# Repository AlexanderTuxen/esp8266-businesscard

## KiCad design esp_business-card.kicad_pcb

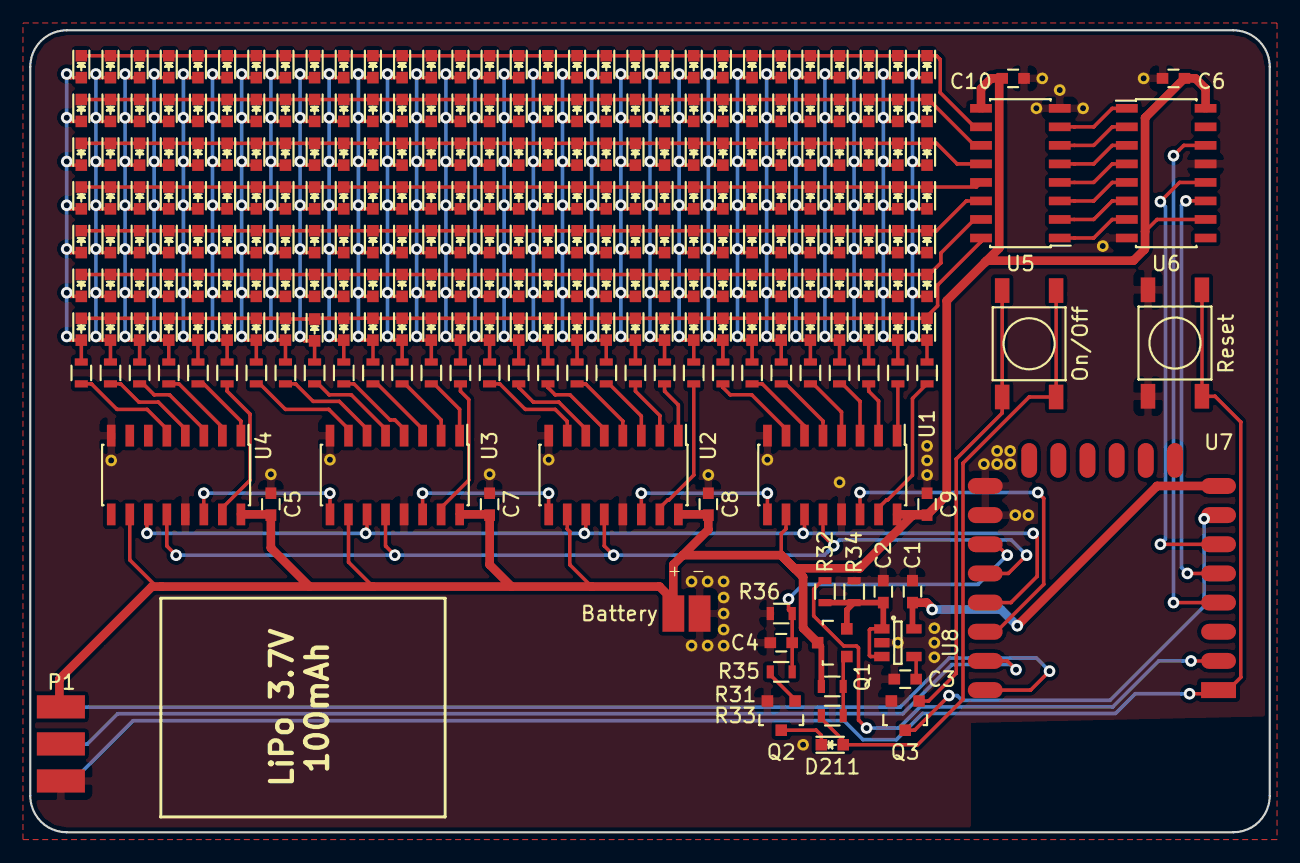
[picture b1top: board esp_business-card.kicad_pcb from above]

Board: 2 copper layers, 85.0 x 55.0 mm, 272 parts (1 on the bottom side), 99 nets.

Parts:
+ -: Battery; motor_pads
C1: 2.2u; C_0603
C2: 1u; C_0603
C3: 4.7u; C_0603
C4: 100n; C_0603
C5, C6, C7, C8, C9, C10: C; C_0603
D1, D2, D3, D4, D5, D6, D7, D8, D9, D10, D11, D12, D13, D14, D15, D16, D17, D18, D19, D20, D21, D22, D23, D24, D25, D26, D27, D28, D29, D30, D31, D32, D33, D34, D35, D36, D37, D38, D39, D40, D41, D42, D43, D44, D45, D46, D47, D48, D49, D50, D51, D52, D53, D54, D55, D56, D57, D58, D59, D60, D61, D62, D63, D64, D65, D66, D67, D68, D69, D70, D71, D72, D73, D74, D75, D76, D77, D78, D79, D80, D81, D82, D83, D84, D85, D86, D87, D88, D89, D90, D91, D92, D93, D94, D95, D96, D97, D98, D99, D100, D101, D102, D103, D104, D105, D106, D107, D108, D109, D110, D111, D112, D113, D114, D115, D116, D117, D118, D119, D120, D121, D122, D123, D124, D125, D126, D127, D128, D129, D130, D131, D132, D133, D134, D135, D136, D137, D138, D139, D140, D141, D142, D143, D144, D145, D146, D147, D148, D149, D150, D151, D152, D153, D154, D155, D156, D157, D158, D159, D160, D161, D162, D163, D164, D165, D166, D167, D168, D169, D170, D171, D172, D173, D174, D175, D176, D177, D178, D179, D180, D181, D182, D183, D184, D185, D186, D187, D188, D189, D190, D191, D192, D193, D194, D195, D196, D197, D198, D199, D200, D201, D202, D203, D204, D205, D206, D207, D208, D209, D210, D211: LED; LED-0603
On/Off: SW_PUSH; BUTTON_5.1
P1: CONN_02X03; 2x3_edge-connector
Q1: Q_PMOS_GSD; SOT-23
Q2, Q3: Q_NMOS_GSD; SOT-23
R1, R2, R3, R4, R5, R6, R7, R8, R9, R10, R11, R12, R13, R14, R15, R16, R17, R18, R19, R20, R21, R22, R23, R24, R25, R26, R27, R28, R29, R30: R; R_0603
R31, R34: 10k; R_0603
R32: 2.2k; R_0603
R33, R35: 1k; R_0603
R36: 330k; R_0603
Reset: SW_PUSH; BUTTON_5.1
U1, U2, U3, U4, U6: 74HC595; SOIC-16_3.9x9.9mm_Pitch1.27mm
U5: ULN2003A; SOIC-16_3.9x9.9mm_Pitch1.27mm
U7: ESP-12E
U8: LP2985LV; SOT-23-5

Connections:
+3V3: C1.1, U7.8, U8.5
/adc: R32.1, U7.2
/auto_off: C4.1, R35.2, R36.1, U7.17
/button_sense: Q3.3, U7.7
/col1: D1.2, D6.2, D11.2, D16.2, D21.2, D26.2, D31.2, R1.1
/col2: D2.2, D7.2, D12.2, D17.2, D22.2, D27.2, D32.2, R5.1
/col3: D3.2, D8.2, D13.2, D18.2, D23.2, D28.2, D33.2, R9.1
/col4: D4.2, D9.2, D14.2, D19.2, D24.2, D29.2, D34.2, R13.1
/col5: D5.2, D10.2, D15.2, D20.2, D25.2, D30.2, D35.2, R17.1
/col6: D36.2, D41.2, D46.2, D51.2, D56.2, D61.2, D66.2, R21.1
/col7: D37.2, D42.2, D47.2, D52.2, D57.2, D62.2, D67.2, R25.1
/col8: D38.2, D43.2, D48.2, D53.2, D58.2, D63.2, D68.2, R28.1
/col9: D39.2, D44.2, D49.2, D54.2, D59.2, D64.2, D69.2, R2.1
/col10: D40.2, D45.2, D50.2, D55.2, D60.2, D65.2, D70.2, R6.1
/col11: D71.2, D76.2, D81.2, D86.2, D91.2, D96.2, D101.2, R10.1
/col12: D72.2, D77.2, D82.2, D87.2, D92.2, D97.2, D102.2, R14.1
/col13: D73.2, D78.2, D83.2, D88.2, D93.2, D98.2, D103.2, R18.1
/col14: D74.2, D79.2, D84.2, D89.2, D94.2, D99.2, D104.2, R22.1
/col15: D75.2, D80.2, D85.2, D90.2, D95.2, D100.2, D105.2, R26.1
/col16: D106.2, D111.2, D116.2, D121.2, D126.2, D131.2, D136.2, R29.1
/col17: D107.2, D112.2, D117.2, D122.2, D127.2, D132.2, D137.2, R3.1
/col18: D108.2, D113.2, D118.2, D123.2, D128.2, D133.2, D138.2, R7.1
/col19: D109.2, D114.2, D119.2, D124.2, D129.2, D134.2, D139.2, R11.1
/col20: D110.2, D115.2, D120.2, D125.2, D130.2, D135.2, D140.2, R15.1
/col21: D141.2, D146.2, D151.2, D156.2, D161.2, D166.2, D171.2, R19.1
/col22: D142.2, D147.2, D152.2, D157.2, D162.2, D167.2, D172.2, R23.1
/col23: D143.2, D148.2, D153.2, D158.2, D163.2, D168.2, D173.2, R27.1
/col24: D144.2, D149.2, D154.2, D159.2, D164.2, D169.2, D174.2, R30.1
/col25: D145.2, D150.2, D155.2, D160.2, D165.2, D170.2, D175.2, R4.1
/col26: D176.2, D181.2, D186.2, D191.2, D196.2, D201.2, D206.2, R8.1
/col27: D177.2, D182.2, D187.2, D192.2, D197.2, D202.2, D207.2, R12.1
/col28: D178.2, D183.2, D188.2, D193.2, D198.2, D203.2, D208.2, R16.1
/col29: D179.2, D184.2, D189.2, D194.2, D199.2, D204.2, D209.2, R20.1
/col30: D180.2, D185.2, D190.2, D195.2, D200.2, D205.2, D210.2, R24.1
/col_rclk: U1.12, U2.12, U3.12, U4.12, U7.18
/col_ser: U1.14, U7.20
/col_srclk: U1.11, U2.11, U3.11, U4.11, U7.19
/rest: P1.6, Reset.2, U7.1
/row1: D1.1, D2.1, D3.1, D4.1, D5.1, D36.1, D37.1, D38.1, D39.1, D40.1, D71.1, D72.1, D73.1, D74.1, D75.1, D106.1, D107.1, D108.1, D109.1, D110.1, D141.1, D142.1, D143.1, D144.1, D145.1, D176.1, D177.1, D178.1, D179.1, D180.1, U5.16
/row2: D6.1, D7.1, D8.1, D9.1, D10.1, D41.1, D42.1, D43.1, D44.1, D45.1, D76.1, D77.1, D78.1, D79.1, D80.1, D111.1, D112.1, D113.1, D114.1, D115.1, D146.1, D147.1, D148.1, D149.1, D150.1, D181.1, D182.1, D183.1, D184.1, D185.1, U5.15
/row3: D11.1, D12.1, D13.1, D14.1, D15.1, D46.1, D47.1, D48.1, D49.1, D50.1, D81.1, D82.1, D83.1, D84.1, D85.1, D116.1, D117.1, D118.1, D119.1, D120.1, D151.1, D152.1, D153.1, D154.1, D155.1, D186.1, D187.1, D188.1, D189.1, D190.1, U5.14
/row4: D16.1, D17.1, D18.1, D19.1, D20.1, D51.1, D52.1, D53.1, D54.1, D55.1, D86.1, D87.1, D88.1, D89.1, D90.1, D121.1, D122.1, D123.1, D124.1, D125.1, D156.1, D157.1, D158.1, D159.1, D160.1, D191.1, D192.1, D193.1, D194.1, D195.1, U5.13
/row5: D21.1, D22.1, D23.1, D24.1, D25.1, D56.1, D57.1, D58.1, D59.1, D60.1, D91.1, D92.1, D93.1, D94.1, D95.1, D126.1, D127.1, D128.1, D129.1, D130.1, D161.1, D162.1, D163.1, D164.1, D165.1, D196.1, D197.1, D198.1, D199.1, D200.1, U5.12
/row6: D26.1, D27.1, D28.1, D29.1, D30.1, D61.1, D62.1, D63.1, D64.1, D65.1, D96.1, D97.1, D98.1, D99.1, D100.1, D131.1, D132.1, D133.1, D134.1, D135.1, D166.1, D167.1, D168.1, D169.1, D170.1, D201.1, D202.1, D203.1, D204.1, D205.1, U5.11
/row7: D31.1, D32.1, D33.1, D34.1, D35.1, D66.1, D67.1, D68.1, D69.1, D70.1, D101.1, D102.1, D103.1, D104.1, D105.1, D136.1, D137.1, D138.1, D139.1, D140.1, D171.1, D172.1, D173.1, D174.1, D175.1, D206.1, D207.1, D208.1, D209.1, D210.1, U5.10
/row_rclk: U6.12, U7.6
/row_ser: U6.14, U7.4
/row_srclk: U6.11, U7.5
/rxd: P1.4, U7.21
/txd: P1.2, U7.22
GND: + -.2, C1.2, C2.2, C3.2, C4.2, C5.2, C6.2, C7.2, C8.2, C9.2, C10.2, P1.5, Q2.2, Q3.2, R34.2, R36.2, Reset.1, U1.8, U1.13, U2.8, U2.13, U3.8, U3.13, U4.8, U4.13, U5.8, U6.8, U6.13, U7.15, U7.16, U8.2
unnamed: C2.1, Q1.2, R32.2, R34.1, U8.1, U8.3
unnamed: C3.1, U8.4
unnamed: D211.1, Q2.3
unnamed: D211.2, On/Off.1, R33.2
unnamed: Q1.1, R31.2, R33.1
unnamed: Q2.1, R35.1
unnamed: On/Off.2, Q3.1
unnamed: R1.2, U1.15
unnamed: R2.2, U2.15
unnamed: R3.2, U3.15
unnamed: R4.2, U4.15
unnamed: R5.2, U1.1
unnamed: R6.2, U2.1
unnamed: R7.2, U3.1
unnamed: R8.2, U4.1
unnamed: R9.2, U1.2
unnamed: R10.2, U2.2
unnamed: R11.2, U3.2
unnamed: R12.2, U4.2
unnamed: R13.2, U1.3
unnamed: R14.2, U2.3
unnamed: R15.2, U3.3
unnamed: R16.2, U4.3
unnamed: R17.2, U1.4
unnamed: R18.2, U2.4
unnamed: R19.2, U3.4
unnamed: R20.2, U4.4
unnamed: R21.2, U1.5
unnamed: R22.2, U2.5
unnamed: R23.2, U3.5
unnamed: R24.2, U4.5
unnamed: R25.2, U1.6
unnamed: R26.2, U2.6
unnamed: R27.2, U3.6
unnamed: R28.2, U1.7
unnamed: R29.2, U2.7
unnamed: R30.2, U3.7
unnamed: U1.9, U2.14
unnamed: U2.9, U3.14
unnamed: U3.9, U4.14
unnamed: U5.1, U6.7
unnamed: U5.2, U6.6
unnamed: U5.3, U6.5
unnamed: U5.4, U6.4
unnamed: U5.5, U6.3
unnamed: U5.6, U6.2
unnamed: U5.7, U6.1
VCC: + -.1, C5.1, C6.1, C7.1, C8.1, C9.1, C10.1, P1.1, Q1.3, R31.1, U1.10, U1.16, U2.10, U2.16, U3.10, U3.16, U4.10, U4.16, U5.9, U6.10, U6.16

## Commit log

2016-07-24 routed and pretty
2016-07-26 charge/programming connector needs to be re-wired
